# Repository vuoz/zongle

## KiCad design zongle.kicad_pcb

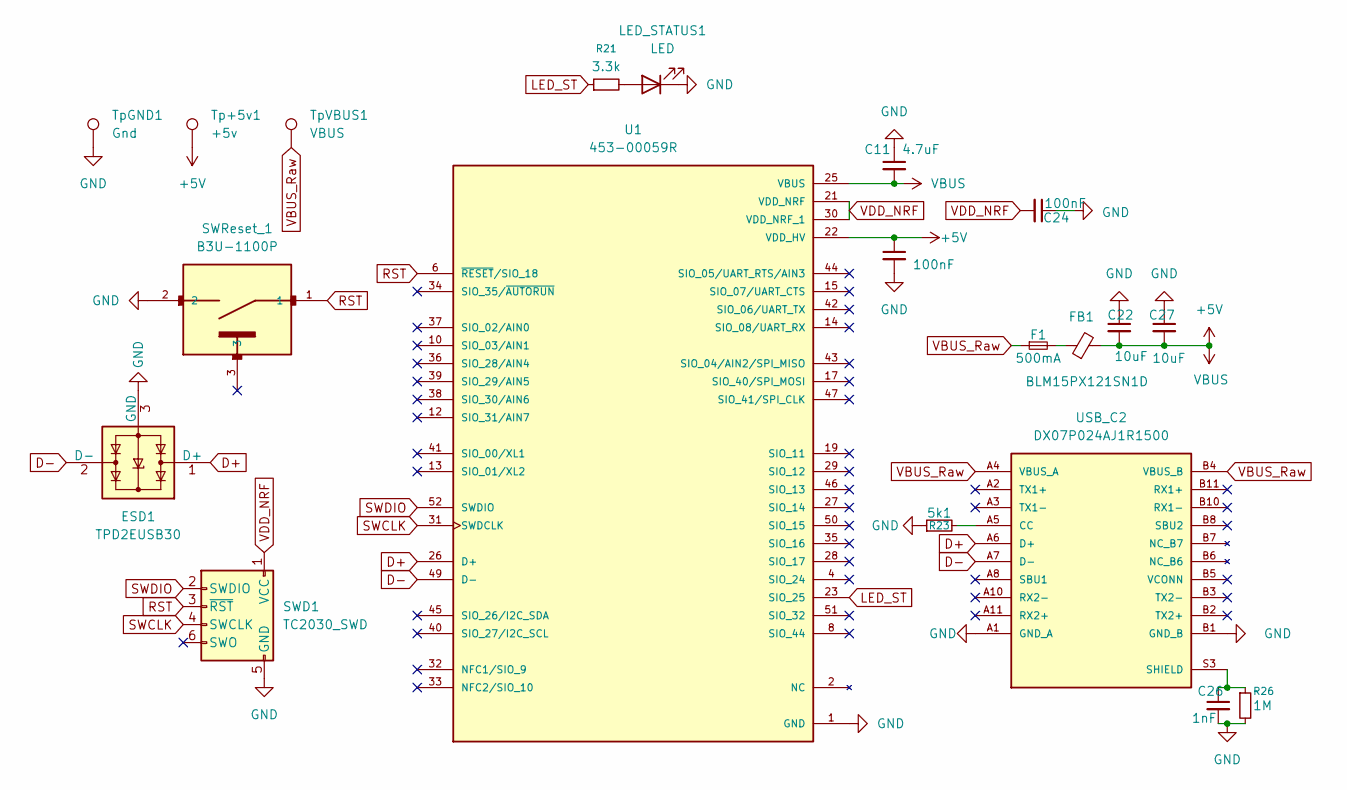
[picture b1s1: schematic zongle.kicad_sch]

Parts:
C11: 4.7uF; C_0402_1005Metric
C22, C27: 10uF; C_0402_1005Metric
C23, C24: 100nF; C_0402_1005Metric
C26: 1nF; C_0402_1005Metric
ESD1: TPD2EUSB30; Texas_DRT-3
F1: 500mA; Fuse_0402_1005Metric
FB1: BLM15PX121SN1D; R_0402_1005Metric
LED_STATUS1: LED; LED_0402_1005Metric
R21: 3.3k; R_0201_0603Metric
R23: 5k1; R_0201_0603Metric
R26: 1M; R_0201_0603Metric
SWD1: TC2030_SWD; CON_TC2030_outlined
SWReset_1: B3U-1100P; SW_SPST_B3U-1000P
Tp+5v1: +5v; TestPoint_Pad_1.0x1.0mm
TpGND1: Gnd; TestPoint_Pad_1.0x1.0mm
TpVBUS1: VBUS; TestPoint_Pad_1.0x1.0mm
U1: 453-00059R; BL653_59; PARTREV 1.5
USB_C2: DX07P024AJ1R1500; USB_C_MALE_LONG; PARTREV January 2016; DigiKey_Part_Number 670-2868-1-ND

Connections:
+5V: C11.2, C22.2, C23.1, C27.2, FB1.2, Tp+5v1.1, U1.22 (VDD_HV), U1.25 (VBUS)
D+: ESD1.1 (D+), U1.26 (D+), USB_C2.A6 (D+)
D-: ESD1.2 (D-), U1.49 (D-), USB_C2.A7 (D-)
GND: C11.1, C22.1, C23.2, C24.1, C26.2, C27.1, ESD1.3 (GND), LED_STATUS1.1 (K), R23.1, R26.2, SWD1.5 (GND), SWReset_1.2, TpGND1.1, U1.1 (GND), U1.3 (GND), U1.5 (GND), U1.7 (GND), U1.9 (GND), U1.11 (GND), U1.16 (GND), U1.18 (GND), U1.20 (GND), U1.24 (GND), U1.48 (GND), U1.G1 (GND), U1.G2 (GND), U1.G3 (GND), U1.G4 (GND), U1.G5 (GND), U1.G6 (GND), U1.G7 (GND), USB_C2.A1 (GND_A), USB_C2.A12 (GND_A), USB_C2.B1 (GND_B), USB_C2.B12 (GND_B)
LED_ST: R21.1, U1.23 (SIO_25)
unnamed: C26.1, R26.1, USB_C2.S3 (SHIELD), USB_C2.S4 (SHIELD), USB_C2.S5 (SHIELD), USB_C2.S6 (SHIELD)
unnamed: F1.2, FB1.1
unnamed: LED_STATUS1.2 (A), R21.2
unnamed: R23.2, USB_C2.A5 (CC)
RST: SWD1.3 (~RST), SWReset_1.1, U1.6 (~RESET/SIO_18)
SWCLK: SWD1.4 (SWCLK), U1.31 (SWDCLK)
SWDIO: SWD1.2 (SWDIO), U1.52 (SWDIO)
VBUS_Raw: F1.1, TpVBUS1.1, USB_C2.A4 (VBUS_A), USB_C2.A9 (VBUS_A), USB_C2.B4 (VBUS_B), USB_C2.B9 (VBUS_B)
VDD_NRF: C24.2, SWD1.1 (VCC), U1.21 (VDD_NRF), U1.30 (VDD_NRF_1)

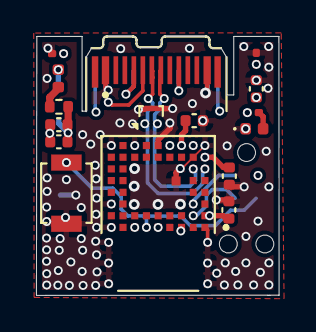
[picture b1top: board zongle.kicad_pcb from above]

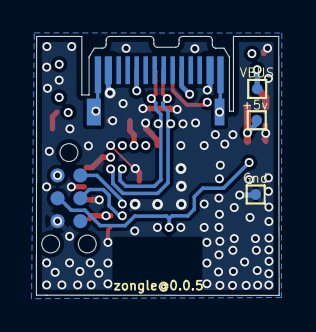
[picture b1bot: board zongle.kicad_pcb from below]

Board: 6 copper layers, 13.5 x 14.4 mm, 20 parts (4 on the bottom side), 14 nets.

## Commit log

2025-12-03 first draft of schematic
2025-12-04 draft of layout
2025-12-06 further routing. still missig footprints for testpoints and reset button, most of the routing is now done, will need some cleanup + drc fixesw
2025-12-07 used actual symbol of usb c port. redid routing. saved 2mm in length. fixed 3d model for usb c receptacle, now using 6 layers for cheap via in pad to avoid having to pay for microvias
2025-12-08 some layout changes. fixed testpoint size. found fitting reset button. moved all parts to the top side, now missing part asignment
2025-12-08 some routing cleanup, some drc fixes, assigned parts to every footprint
2025-12-08 minor changes to the routing. final tweaks for first version
2025-12-08 added version indicator on pcb
2025-12-09 moved some components furhter from the antenna, modified usb testpoints to be smaller and not interfere with the signal (hopefully :o ), changed track width to 0.2mm on most components to avoid produ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
2025-12-10 some tweaks to usb routing. move power cap closer to vdd
2025-12-10 linked model for 453-00059 nrf52833 module, later will move all the modules to the project repo, so that using this on another device is possible without new linking of the models
2025-12-10 minor changes
2025-12-11 moved all power traces to inner layers. added some via stitching
2025-12-11 some more cleanup. changed zone fill properties to match design requirements. moved led trace to power layer, more via stitching
2025-12-11 moved led outside of antenna perimeter just to be extra sure. some via stitching + cleanup
2025-12-11 moved testpad for 5v to allow via in pad for decoupeling cap instead of trace to a far away via
2025-12-11 removed usb testpoints
2025-12-11 cleaned usb traces. moved esd closer to usb
2025-12-12 moved testpoints
2025-12-16 some routing refinements. moved all components as far away from the antenna as possible. added another decup cap to the power path. changed board thickness to 0.8mm to accomodate for usb-c plug. some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
2025-12-17 changes version number to 0.0.5
2025-12-17 moved via minimally
